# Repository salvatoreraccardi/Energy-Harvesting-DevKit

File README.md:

# OBJEX EHDK - Energy harvesting DevKit 

I designed this PCB(OBJEX EHDK) to study energy harvesting more closely, so I compared two energy harvesters(SPV1050 & ADP5091) to understand their operation and differences.

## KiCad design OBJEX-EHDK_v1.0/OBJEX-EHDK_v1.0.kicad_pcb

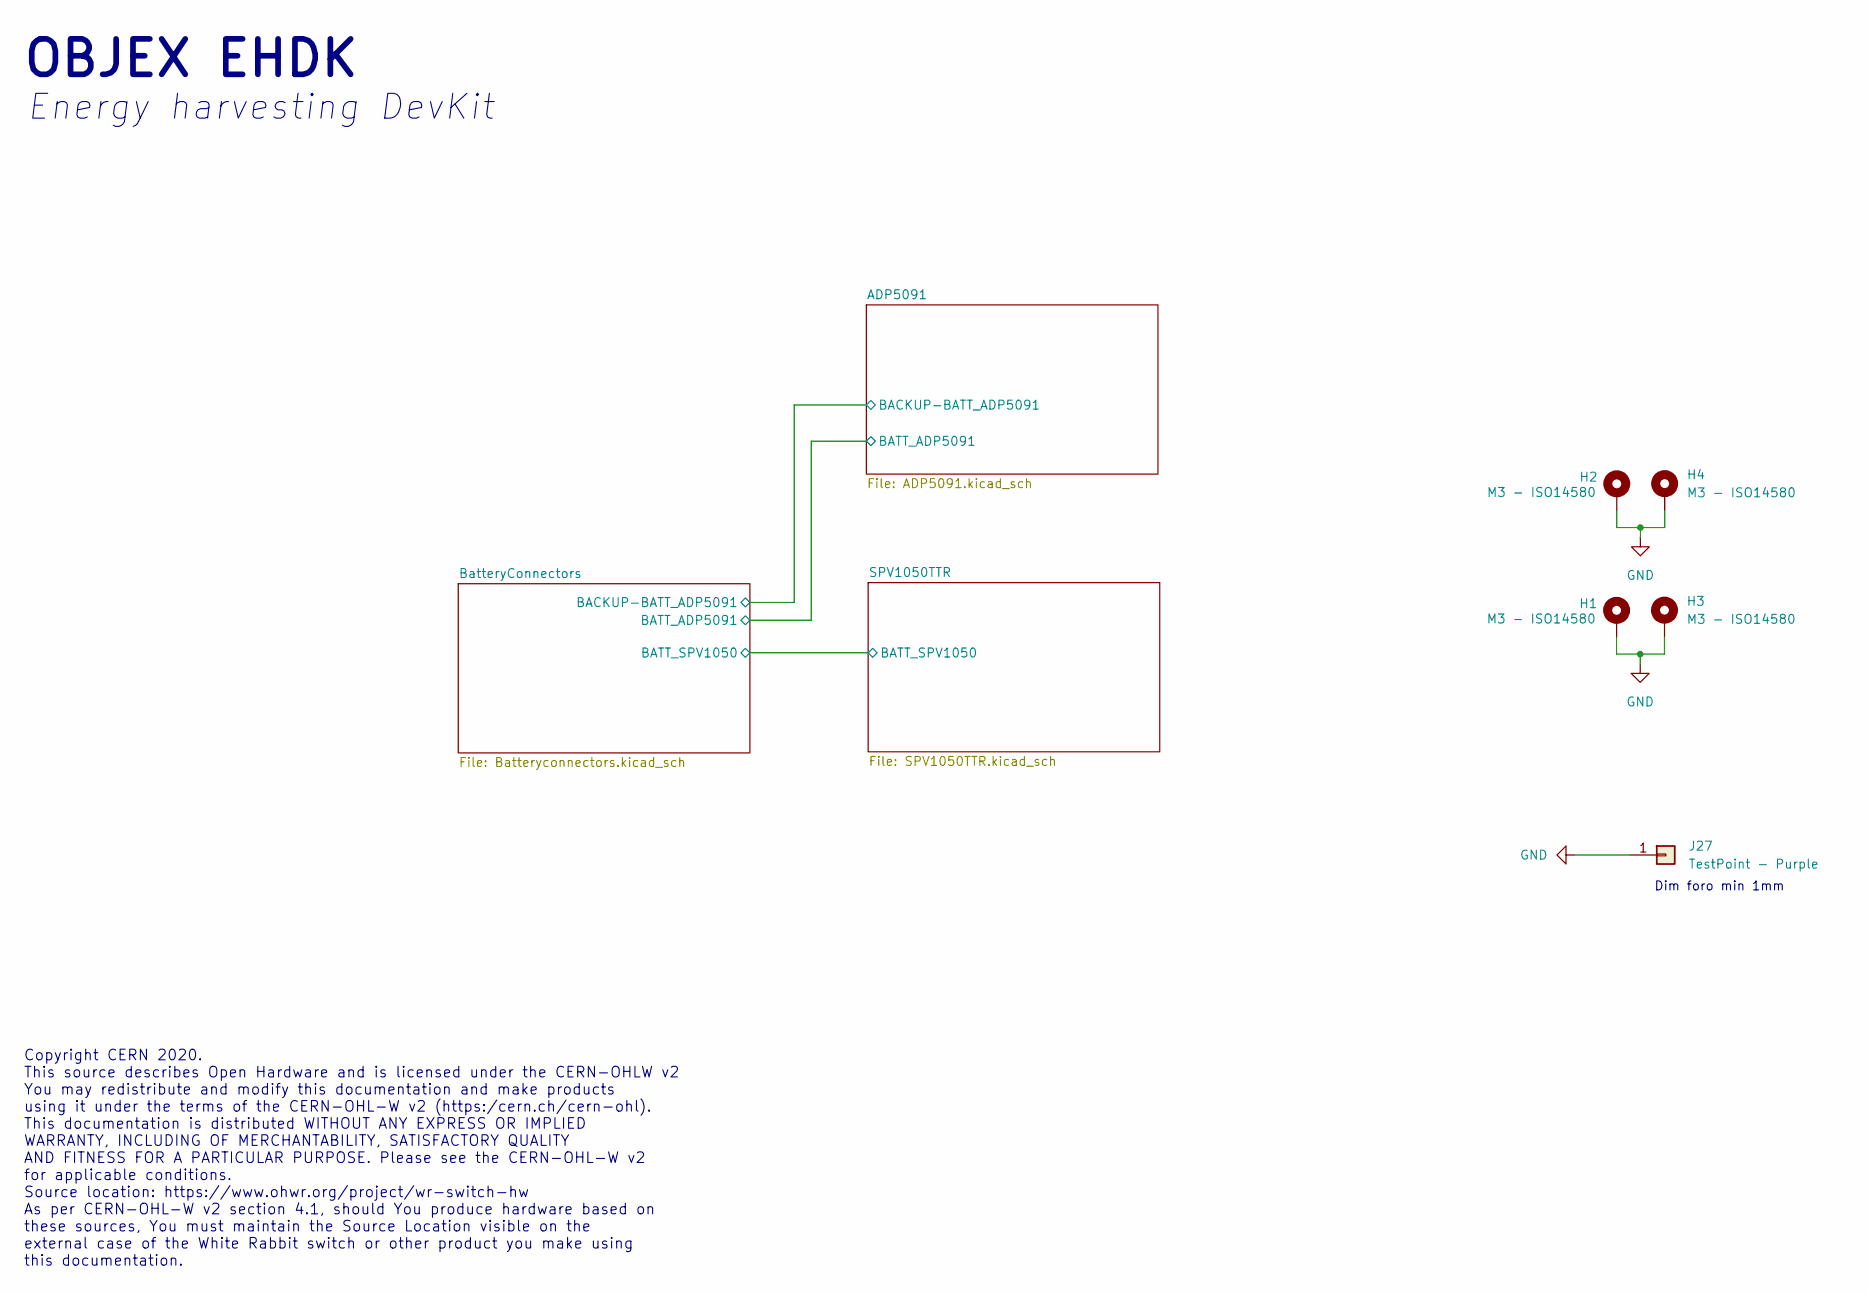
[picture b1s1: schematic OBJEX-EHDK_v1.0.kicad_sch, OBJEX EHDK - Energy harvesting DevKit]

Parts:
H1, H2, H3, H4: M3 - ISO14580; MountingHole_3.2mm_M3_ISO14580_Pad
J27: TestPoint - Purple; TestPoint_Loop_D3.80mm_Drill2.0mm

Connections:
GND: H1.1, H2.1, H3.1, H4.1, J27.1; also elsewhere on the board

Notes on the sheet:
Dim foro min 1mm
OBJEX EHDK
Copyright CERN 2020. This source describes Open Hardware and is licensed under the CERN-OHLW v2 You may redistribute and modify this documentation and make products using it under the terms of the CERN-OHL-W v2 (https:/cern.ch/cern-ohl). This documentation is distributed WITHOUT ANY EXPRESS OR IMPL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
Energy harvesting DevKit

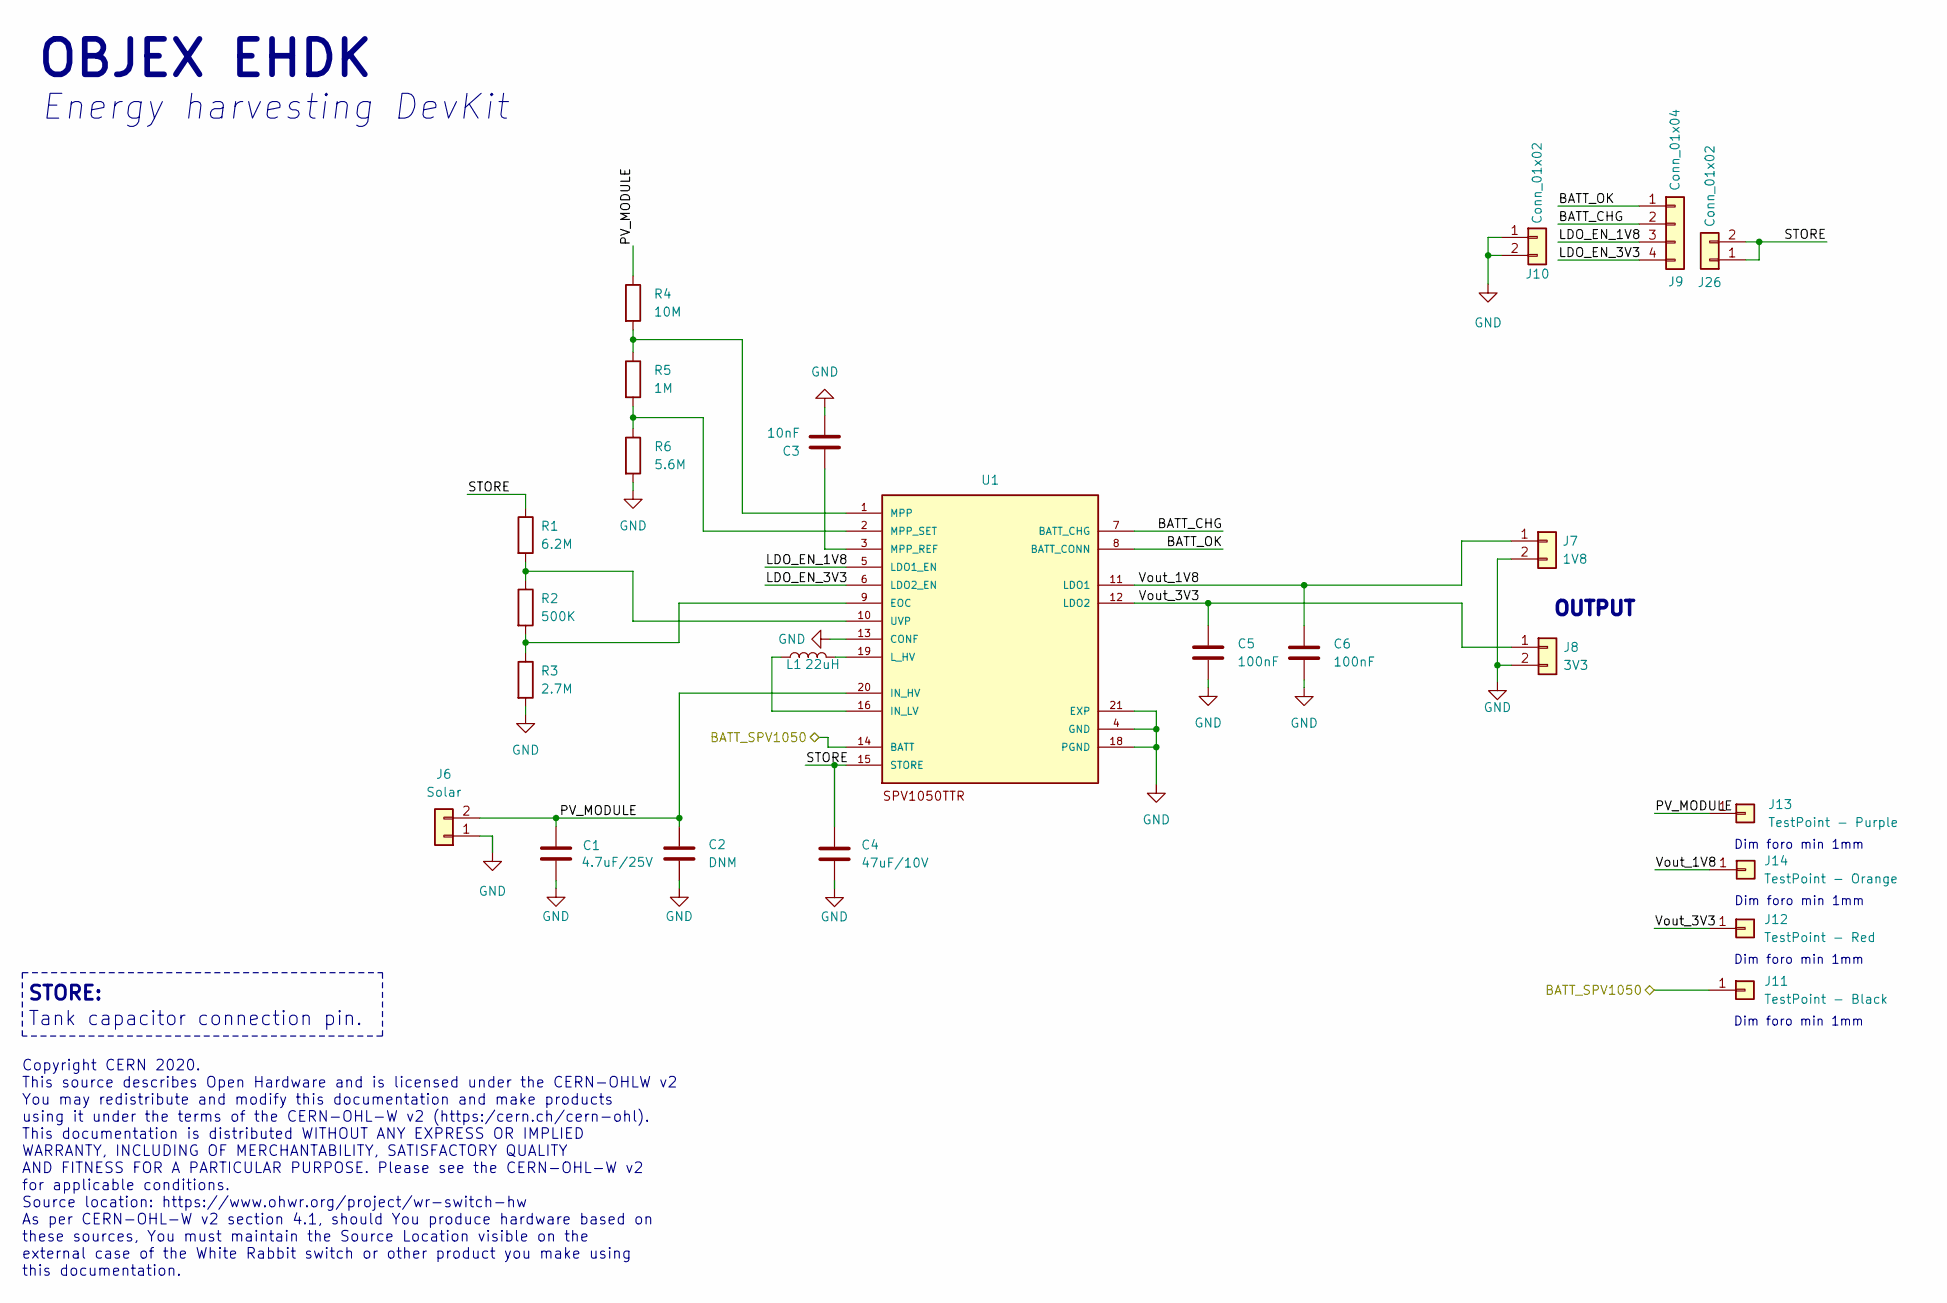
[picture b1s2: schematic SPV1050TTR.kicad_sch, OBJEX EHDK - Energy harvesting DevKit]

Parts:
C1: 4.7uF/25V; C_0603_1608Metric
C2: DNM; C_0603_1608Metric
C3: 10nF; C_0402_1005Metric
C4: 47uF/10V; C_0805_2012Metric
C5, C6: 100nF; C_0402_1005Metric
J6: Solar; PinHeader_1x02_P2.54mm_Vertical
J7: 1V8; PinHeader_1x02_P2.54mm_Vertical
J8: 3V3; PinHeader_1x02_P2.54mm_Vertical
J9: Conn_01x04; PinHeader_1x04_P2.54mm_Vertical
J10, J26: Conn_01x02; PinHeader_1x02_P2.54mm_Vertical
J11: TestPoint - Black; TestPoint_Loop_D3.80mm_Drill2.0mm
J12: TestPoint - Red; TestPoint_Loop_D3.80mm_Drill2.0mm
J13: TestPoint - Purple; TestPoint_Loop_D3.80mm_Drill2.0mm
J14: TestPoint - Orange; TestPoint_Loop_D3.80mm_Drill2.0mm
L1: 22uH; L_0603_1608Metric
R1: 6.2M; R_0603_1608Metric
R2: 500K; R_0603_1608Metric
R3: 2.7M; R_0603_1608Metric
R4: 10M; R_0603_1608Metric
R5: 1M; R_0603_1608Metric
R6: 5.6M; R_0603_1608Metric
U1: SPV1050TTR; QFN40P300X300X100-21N

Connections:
/BatteryConnectors/BATT_SPV1050: J11.1, U1.14 (BATT); also elsewhere on the board
/SPV1050TTR/BATT_CHG: J9.2, U1.7 (BATT_CHG)
/SPV1050TTR/BATT_OK: J9.1, U1.8 (BATT_CONN)
/SPV1050TTR/LDO_EN_1V8: J9.3, U1.5 (LDO1_EN)
/SPV1050TTR/LDO_EN_3V3: J9.4, U1.6 (LDO2_EN)
/SPV1050TTR/PV_MODULE: C1.1, C2.1, J6.2, J13.1, R4.1, U1.20 (IN_HV)
/SPV1050TTR/STORE: C4.1, J26.1, J26.2, R1.1, U1.15 (STORE)
/SPV1050TTR/Vout_1V8: C6.1, J7.1, J14.1, U1.11 (LDO1)
/SPV1050TTR/Vout_3V3: C5.1, J8.1, J12.1, U1.12 (LDO2)
GND: C1.2, C2.2, C3.2, C4.2, C5.2, C6.2, J6.1, J7.2, J8.2, J10.1, J10.2, R3.2, R6.2, U1.4 (GND), U1.13 (CONF), U1.18 (PGND), U1.21 (EXP); also elsewhere on the board
unnamed: C3.1, U1.3 (MPP_REF)
unnamed: L1.1, U1.16 (IN_LV)
unnamed: L1.2, U1.19 (L_HV)
unnamed: R1.2, R2.1, U1.10 (UVP)
unnamed: R2.2, R3.1, U1.9 (EOC)
unnamed: R4.2, R5.1, U1.1 (MPP)
unnamed: R5.2, R6.1, U1.2 (MPP_SET)

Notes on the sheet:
Dim foro min 1mm
Copyright CERN 2020. This source describes Open Hardware and is licensed under the CERN-OHLW v2 You may redistribute and modify this documentation and make products using it under the terms of the CERN-OHL-W v2 (https:/cern.ch/cern-ohl). This documentation is distributed WITHOUT ANY EXPRESS OR IMPL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
OUTPUT
OBJEX EHDK
Energy harvesting DevKit
Tank capacitor connection pin.
STORE:

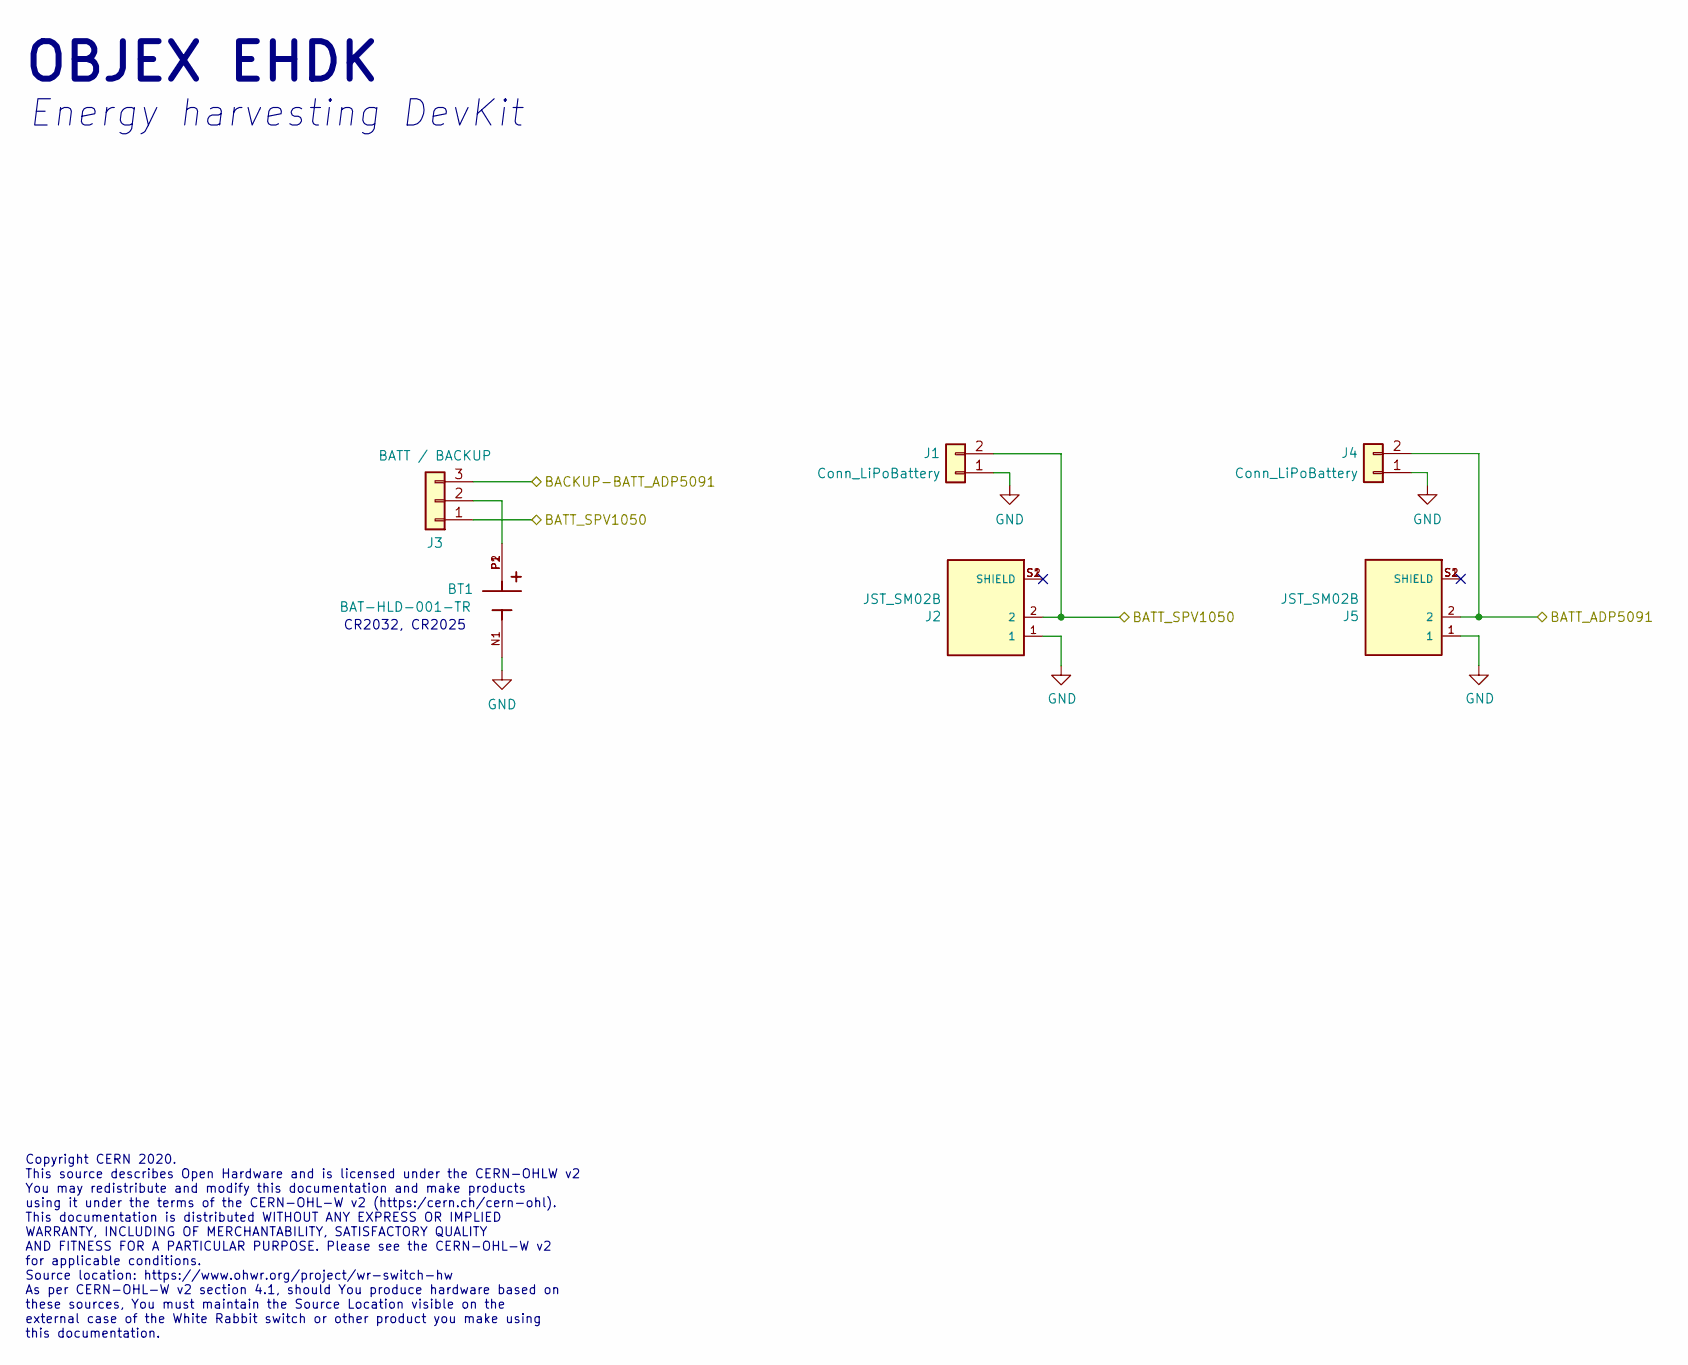
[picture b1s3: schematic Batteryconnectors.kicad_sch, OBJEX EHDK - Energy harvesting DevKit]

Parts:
BT1: BAT-HLD-001-TR; BAT_BAT-HLD-001-TR; PARTREV B
J1, J4: Conn_LiPoBattery; PinHeader_1x02_P2.54mm_Vertical
J2, J5: JST_SM02B; JST_SM02B-SURS-TF(LF)(SN); PARTREV N/A
J3: BATT / BACKUP; PinHeader_1x03_P2.54mm_Vertical

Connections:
/ADP5091/BACKUP-BATT_ADP5091: J3.3; also elsewhere on the board
/ADP5091/BATT_ADP5091: J4.2, J5.2; also elsewhere on the board
/BatteryConnectors/BATT_SPV1050: J1.2, J2.2, J3.1; also elsewhere on the board
GND: BT1.N1, J1.1, J2.1, J4.1, J5.1; also elsewhere on the board
unnamed: BT1.P1, BT1.P2, J3.2

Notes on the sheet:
CR2032, CR2025
Copyright CERN 2020. This source describes Open Hardware and is licensed under the CERN-OHLW v2 You may redistribute and modify this documentation and make products using it under the terms of the CERN-OHL-W v2 (https:/cern.ch/cern-ohl). This documentation is distributed WITHOUT ANY EXPRESS OR IMPL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
OBJEX EHDK
Energy harvesting DevKit

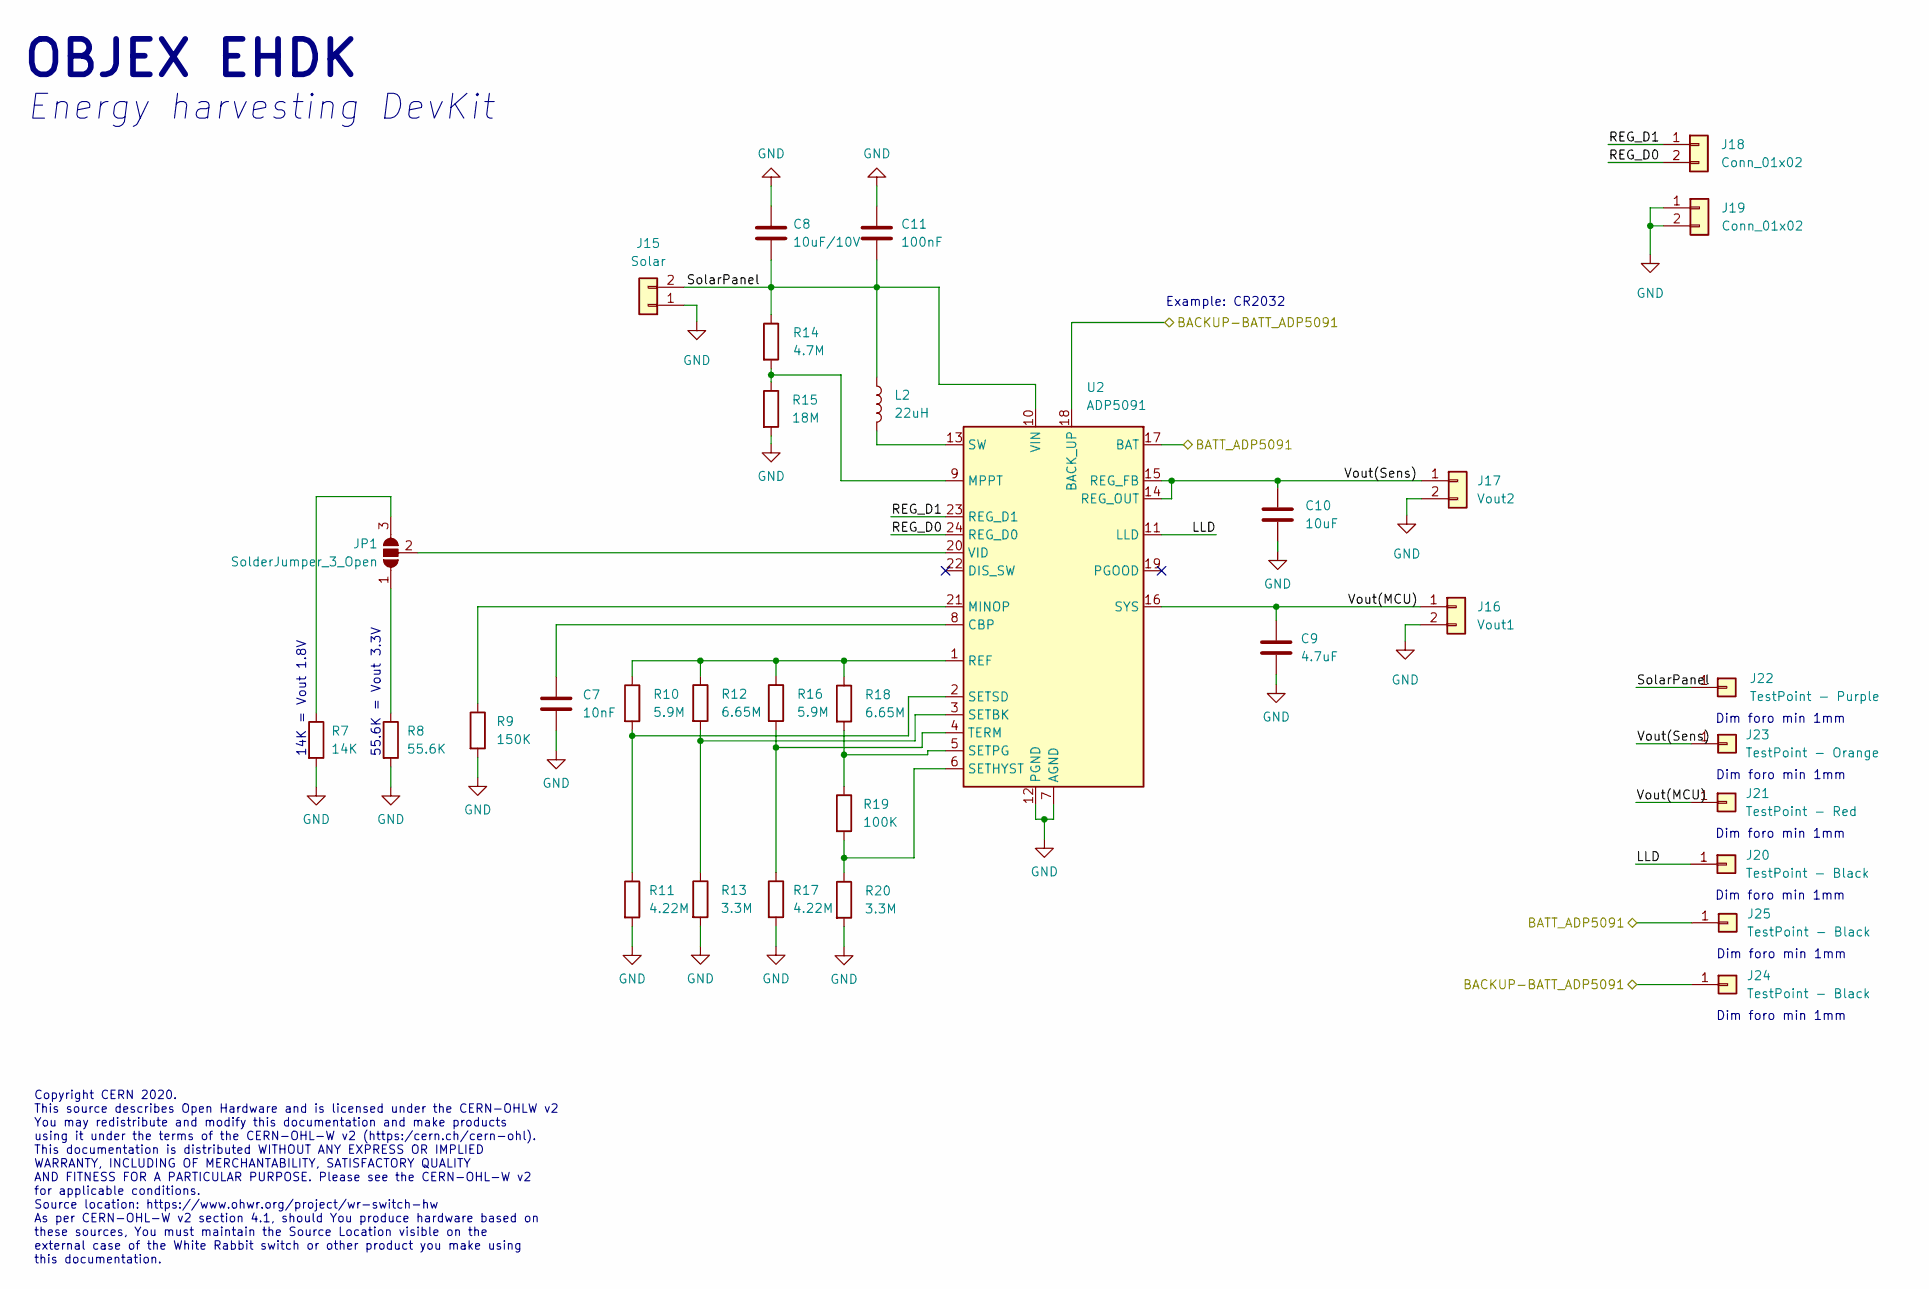
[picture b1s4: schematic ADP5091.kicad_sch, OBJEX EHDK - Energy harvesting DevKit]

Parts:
C7: 10nF; C_0402_1005Metric
C8: 10uF/10V; C_0402_1005Metric
C9: 4.7uF; C_0603_1608Metric
C10: 10uF; C_0603_1608Metric
C11: 100nF; C_0402_1005Metric
J15: Solar; PinHeader_1x02_P2.54mm_Vertical
J16: Vout1; PinHeader_1x02_P2.54mm_Vertical
J17: Vout2; PinHeader_1x02_P2.54mm_Vertical
J18, J19: Conn_01x02; PinHeader_1x02_P2.54mm_Vertical
J20, J24, J25: TestPoint - Black; TestPoint_Loop_D3.80mm_Drill2.0mm
J21: TestPoint - Red; TestPoint_Loop_D3.80mm_Drill2.0mm
J22: TestPoint - Purple; TestPoint_Loop_D3.80mm_Drill2.0mm
J23: TestPoint - Orange; TestPoint_Loop_D3.80mm_Drill2.0mm
JP1: SolderJumper_3_Open; SolderJumper-3_P1.3mm_Open_Pad1.0x1.5mm_NumberLabels
L2: 22uH; L_0603_1608Metric
R7: 14K; R_0603_1608Metric
R8: 55.6K; R_0603_1608Metric
R9: 150K; R_0603_1608Metric
R10, R16: 5.9M; R_0603_1608Metric
R11, R17: 4.22M; R_0603_1608Metric
R12, R18: 6.65M; R_0603_1608Metric
R13, R20: 3.3M; R_0603_1608Metric
R14: 4.7M; R_0603_1608Metric
R15: 18M; R_0603_1608Metric
R19: 100K; R_0603_1608Metric
U2: ADP5091; LFCSP-24-1EP_4x4mm_P0.5mm_EP2.3x2.3mm

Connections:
/ADP5091/BACKUP-BATT_ADP5091: J24.1, U2.18 (BACK_UP); also elsewhere on the board
/ADP5091/BATT_ADP5091: J25.1, U2.17 (BAT); also elsewhere on the board
/ADP5091/LLD: J20.1, U2.11 (LLD)
/ADP5091/REG_D0: J18.2, U2.24 (REG_D0)
/ADP5091/REG_D1: J18.1, U2.23 (REG_D1)
/ADP5091/SolarPanel: C8.2, C11.2, J15.2, J22.1, L2.1, R14.1, U2.10 (VIN)
/ADP5091/Vout(MCU): C9.1, J16.1, J21.1, U2.16 (SYS)
/ADP5091/Vout(Sens): C10.1, J17.1, J23.1, U2.14 (REG_OUT), U2.15 (REG_FB)
GND: C7.2, C8.1, C9.2, C10.2, C11.1, J15.1, J16.2, J17.2, J19.1, J19.2, R7.2, R8.2, R9.2, R11.2, R13.2, R15.2, R17.2, R20.2, U2.7 (AGND), U2.12 (PGND), U2.25 (AGND); also elsewhere on the board
unnamed: C7.1, U2.8 (CBP)
unnamed: JP1.1 (A), R8.1
unnamed: JP1.2 (C), U2.20 (VID)
unnamed: JP1.3 (B), R7.1
unnamed: L2.2, U2.13 (SW)
unnamed: R9.1, U2.21 (MINOP)
unnamed: R10.1, R12.1, R16.1, R18.1, U2.1 (REF)
unnamed: R10.2, R11.1, U2.2 (SETSD)
unnamed: R12.2, R13.1, U2.3 (SETBK)
unnamed: R14.2, R15.1, U2.9 (MPPT)
unnamed: R16.2, R17.1, U2.4 (TERM)
unnamed: R18.2, R19.1, U2.5 (SETPG)
unnamed: R19.2, R20.1, U2.6 (SETHYST)

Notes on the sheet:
Copyright CERN 2020. This source describes Open Hardware and is licensed under the CERN-OHLW v2 You may redistribute and modify this documentation and make products using it under the terms of the CERN-OHL-W v2 (https:/cern.ch/cern-ohl). This documentation is distributed WITHOUT ANY EXPRESS OR IMPL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
Dim foro min 1mm
OBJEX EHDK
55.6K = Vout 3.3V
Example: CR2032
Energy harvesting DevKit
14K = Vout 1.8V

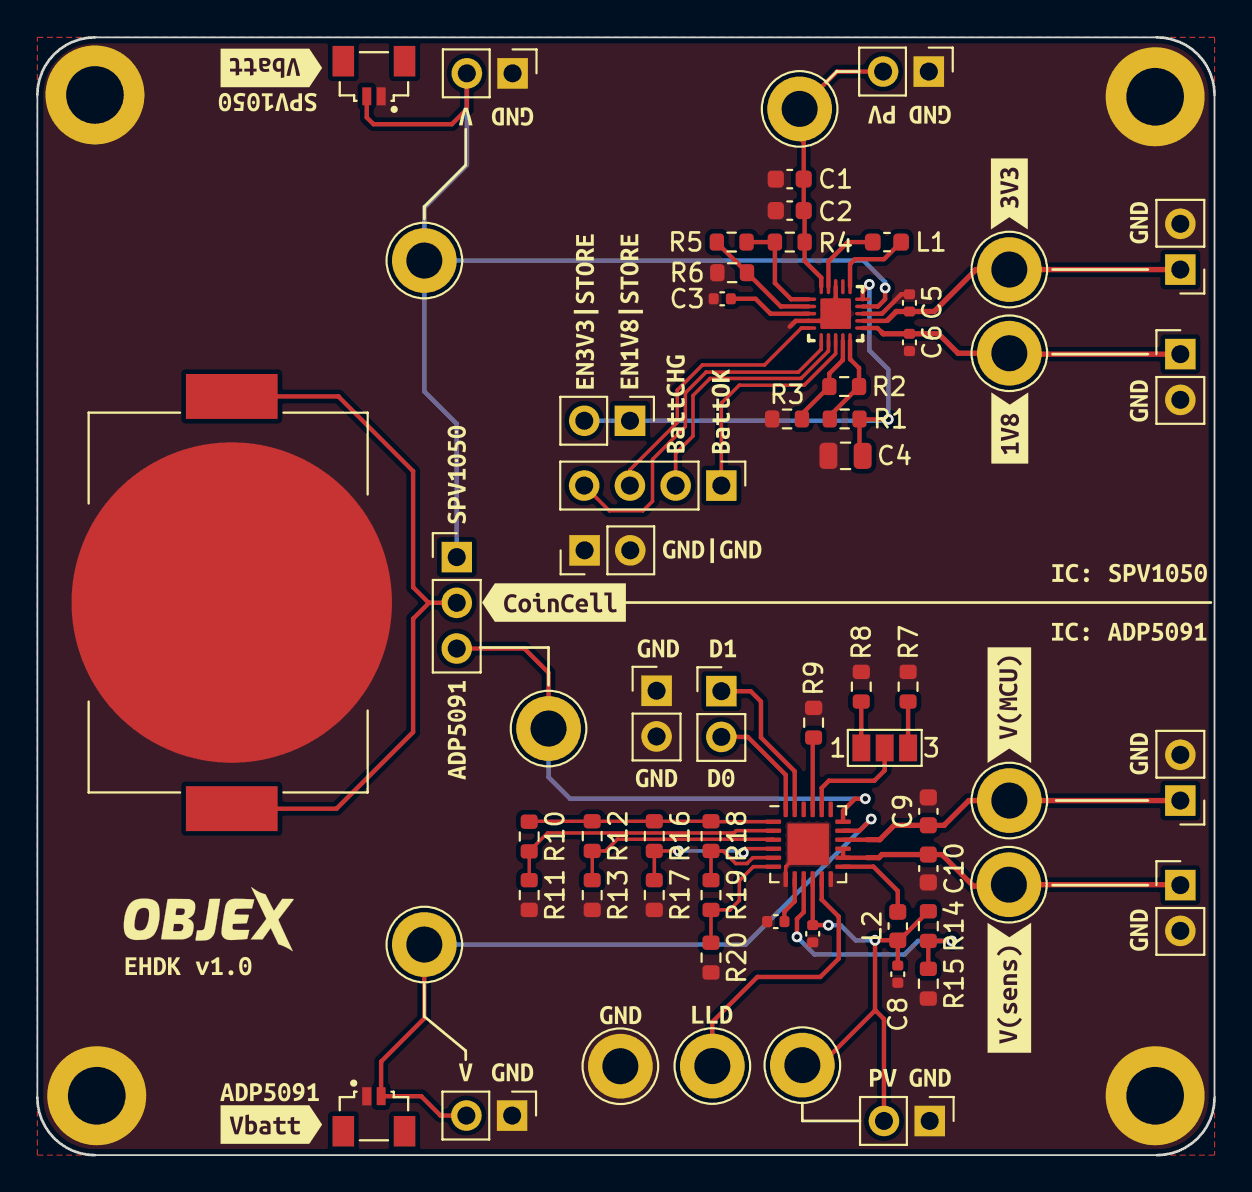
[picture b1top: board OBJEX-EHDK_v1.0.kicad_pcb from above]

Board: 2 copper layers, 65.4 x 62.1 mm, 105 parts (0 on the bottom side), 39 nets.

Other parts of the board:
kibuzzard-630A2C1A, kibuzzard-630A2C1A#2: G***; kibuzzard-630A2C1A
kibuzzard-630A2CD4: G***; kibuzzard-630A2CD4
kibuzzard-630DCDF3: G***; kibuzzard-630DCDF3
kibuzzard-630DD2B3: G***; kibuzzard-630DD2B3
kibuzzard-630DD2DE: G***; kibuzzard-630DD2DE
kibuzzard-630DD25A: G***; kibuzzard-630DD25A
kibuzzard-630DD246: G***; kibuzzard-630DD246
kibuzzard-630DD299: G***; kibuzzard-630DD299
kibuzzard-630DD324: G***; kibuzzard-630DD324
kibuzzard-630DD339: G***; kibuzzard-630DD339
kibuzzard-6307AAC8: G***; kibuzzard-6307AAC8
kibuzzard-6307AB03: G***; kibuzzard-6307AB03
kibuzzard-6307AB8B, kibuzzard-6307AB8B#2, kibuzzard-6307AB8B#3, kibuzzard-6307AB8B#4, kibuzzard-6307AB8B#5, kibuzzard-6307AB8B#6, kibuzzard-6307AB8B#7, kibuzzard-6307AB8B#8, kibuzzard-6307AB8B#9, kibuzzard-6307AB8B#10, kibuzzard-6307AB8B#11: G***; kibuzzard-6307AB8B
kibuzzard-6307AB19: G***; kibuzzard-6307AB19
kibuzzard-6307AD03: G***; kibuzzard-6307AD03
kibuzzard-6307AD08: G***; kibuzzard-6307AD08
kibuzzard-6307AD98: G***; kibuzzard-6307AD98
kibuzzard-6307B6B8, kibuzzard-6307B6B8#2: G***; kibuzzard-6307B6B8
kibuzzard-6307B74A: G***; kibuzzard-6307B74A
kibuzzard-6307B77B: G***; kibuzzard-6307B77B
kibuzzard-6307B472, kibuzzard-6307B472#2: G***; kibuzzard-6307B472
kibuzzard-6307B497, kibuzzard-6307B497#2: G***; kibuzzard-6307B497
kibuzzard-6307B557: G***; kibuzzard-6307B557

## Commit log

2022-07-23 Init push
2022-07-23 LICENSE
2022-07-23 Battery Connectors & Battery LVL circuits
2022-07-23 add: nRF52840 & SPV1050TTR
2022-07-23 add docs
2022-07-25 add: ADP5091
2022-08-07 Update design, EH ICs & Battery conn
2022-08-18 fix some things
2022-08-18 update sch
2022-08-19 Fix, add test points
2022-08-19 SCH Ready for first review
2022-08-20 SCH Ready for PCB design
2022-08-20 SCH first review
2022-08-21 PCB design update
2022-08-25 update design
2022-08-30 last review
2022-08-31 PCBWay order ready!
2022-10-17 init

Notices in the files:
OBJEX-EHDK_v1.0/ADP5091.kicad_sch:
As per CERN-OHL-W v2 section 4.1, should You produce hardware based on
